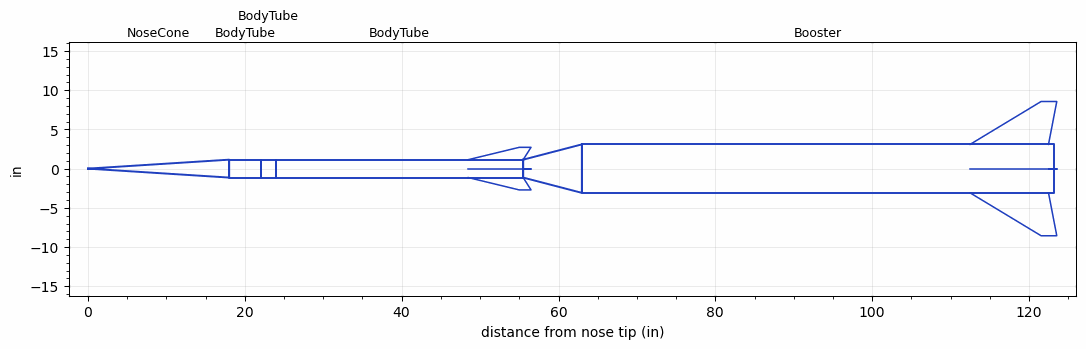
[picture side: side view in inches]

<RASAeroDocument>
 <FileVersion>2</FileVersion>
 <RocketDesign>
  <NoseCone>
   <Length>18</Length>
   <Diameter>2.2835</Diameter>
   <Shape>Conical</Shape>
   <Location>0</Location>
  </NoseCone>
  <BodyTube>
   <Length>4</Length>
   <Diameter>2.2835</Diameter>
   <Location>18</Location>
  </BodyTube>
  <BodyTube>
   <Length>2</Length>
   <Diameter>2.2835</Diameter>
   <Location>22</Location>
  </BodyTube>
  <BodyTube>
   <Length>31.496</Length>
   <Diameter>2.2835</Diameter>
   <Location>24</Location>
   <Fin>
    <Count>4</Count>
    <Chord>7</Chord>
    <Span>1.5748</Span>
    <SweepDistance>6.5</SweepDistance>
    <TipChord>1.5</TipChord>
    <Thickness>0.0787</Thickness>
    <Location>7</Location>
    <AirfoilSection>Rounded</AirfoilSection>
   </Fin>
  </BodyTube>
  <Booster>
   <Length>60.2617</Length>
   <Diameter>6.1811</Diameter>
   <InsideDiameter>2.2835</InsideDiameter>
   <Location>55.496</Location>
   <ShoulderLength>7.4803</ShoulderLength>
   <Fin>
    <Count>4</Count>
    <Chord>10</Chord>
    <Span>5.4685</Span>
    <SweepDistance>9.0551</SweepDistance>
    <TipChord>2</TipChord>
    <Thickness>0.0787</Thickness>
    <Location>10.75</Location>
    <AirfoilSection>Rounded</AirfoilSection>
   </Fin>
  </Booster>
  <Surface>Camouflage Paint</Surface>
  <ModifiedBarrowman>False</ModifiedBarrowman>
  <Turbulence>False</Turbulence>
  <UseBooster1>True</UseBooster1>
  <UseBooster2>False</UseBooster2>
 </RocketDesign>
 <LaunchSite>
  <Altitude>0</Altitude>
  <Pressure>29.9214</Pressure>
  <RodAngle>0</RodAngle>
  <RodLength>39.37</RodLength>
  <Temperature>59</Temperature>
  <WindSpeed>4.4739</WindSpeed>
 </LaunchSite>
 <Recovery>
  <Altitude1>656.168</Altitude1>
  <Altitude2>0</Altitude2>
  <DeviceType1>Parachute</DeviceType1>
  <DeviceType2>None</DeviceType2>
  <Event1>True</Event1>
  <Event2>False</Event2>
  <Size1>47.9999</Size1>
  <Size2>0</Size2>
  <EventType1>Apogee</EventType1>
  <EventType2>None</EventType2>
  <CD1>0.8</CD1>
  <CD2>0</CD2>
 </Recovery>
 <SimulationList>
  <Simulation>
   <SustainerEngine>K250W-20case  (AT)</SustainerEngine>
   <SustainerLaunchWt>6.4</SustainerLaunchWt>
   <SustainerCG>34.5</SustainerCG>
   <SustainerIgnitionDelay>17</SustainerIgnitionDelay>
   <Booster1Engine>O6926  (TRT)</Booster1Engine>
   <Booster1LaunchWt>60</Booster1LaunchWt>
   <Booster1SeparationDelay>0</Booster1SeparationDelay>
   <Booster1IgnitionDelay>0</Booster1IgnitionDelay>
   <Booster1CG>87.68</Booster1CG>
   <IncludeBooster1>True</IncludeBooster1>
   <Booster2Delay>0</Booster2Delay>
   <IncludeBooster2>False</IncludeBooster2>
   <TimetoApogee>156.5359</TimetoApogee>
   <MaxAltitude>330517</MaxAltitude>
   <MaxVelocity>4358.533</MaxVelocity>
  </Simulation>
  <Simulation>
   <SustainerLaunchWt>3.3097</SustainerLaunchWt>
   <SustainerCG>26.262</SustainerCG>
   <SustainerIgnitionDelay>0</SustainerIgnitionDelay>
   <Booster1LaunchWt>18.8915</Booster1LaunchWt>
   <Booster1SeparationDelay>0</Booster1SeparationDelay>
   <Booster1IgnitionDelay>0</Booster1IgnitionDelay>
   <Booster1CG>72.8954</Booster1CG>
   <IncludeBooster1>False</IncludeBooster1>
   <Booster2Delay>0</Booster2Delay>
   <IncludeBooster2>False</IncludeBooster2>
  </Simulation>
  <Simulation>
   <SustainerLaunchWt>3.3097</SustainerLaunchWt>
   <SustainerCG>26.262</SustainerCG>
   <SustainerIgnitionDelay>0</SustainerIgnitionDelay>
   <Booster1LaunchWt>18.8915</Booster1LaunchWt>
   <Booster1SeparationDelay>0</Booster1SeparationDelay>
   <Booster1IgnitionDelay>0</Booster1IgnitionDelay>
   <Booster1CG>72.8954</Booster1CG>
   <IncludeBooster1>False</IncludeBooster1>
   <Booster2Delay>0</Booster2Delay>
   <IncludeBooster2>False</IncludeBooster2>
  </Simulation>
 </SimulationList>
</RASAeroDocument>
